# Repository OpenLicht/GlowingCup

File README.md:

# Glowing Cup

## Summary
The board measures the temperature and adjusts the color accordingly.
The Temperature is determined by three sensors, which provides the mean value
to the microcontroller. It processes and visualizes the data as a color via the built-in RGB LEDs. The board is charged wirelessly using Qi(pronounced CHEE) technology.

## Pictures
|                                    |                                |
| ---------------------              | ---------------------          |
|     |  |
|  |  |

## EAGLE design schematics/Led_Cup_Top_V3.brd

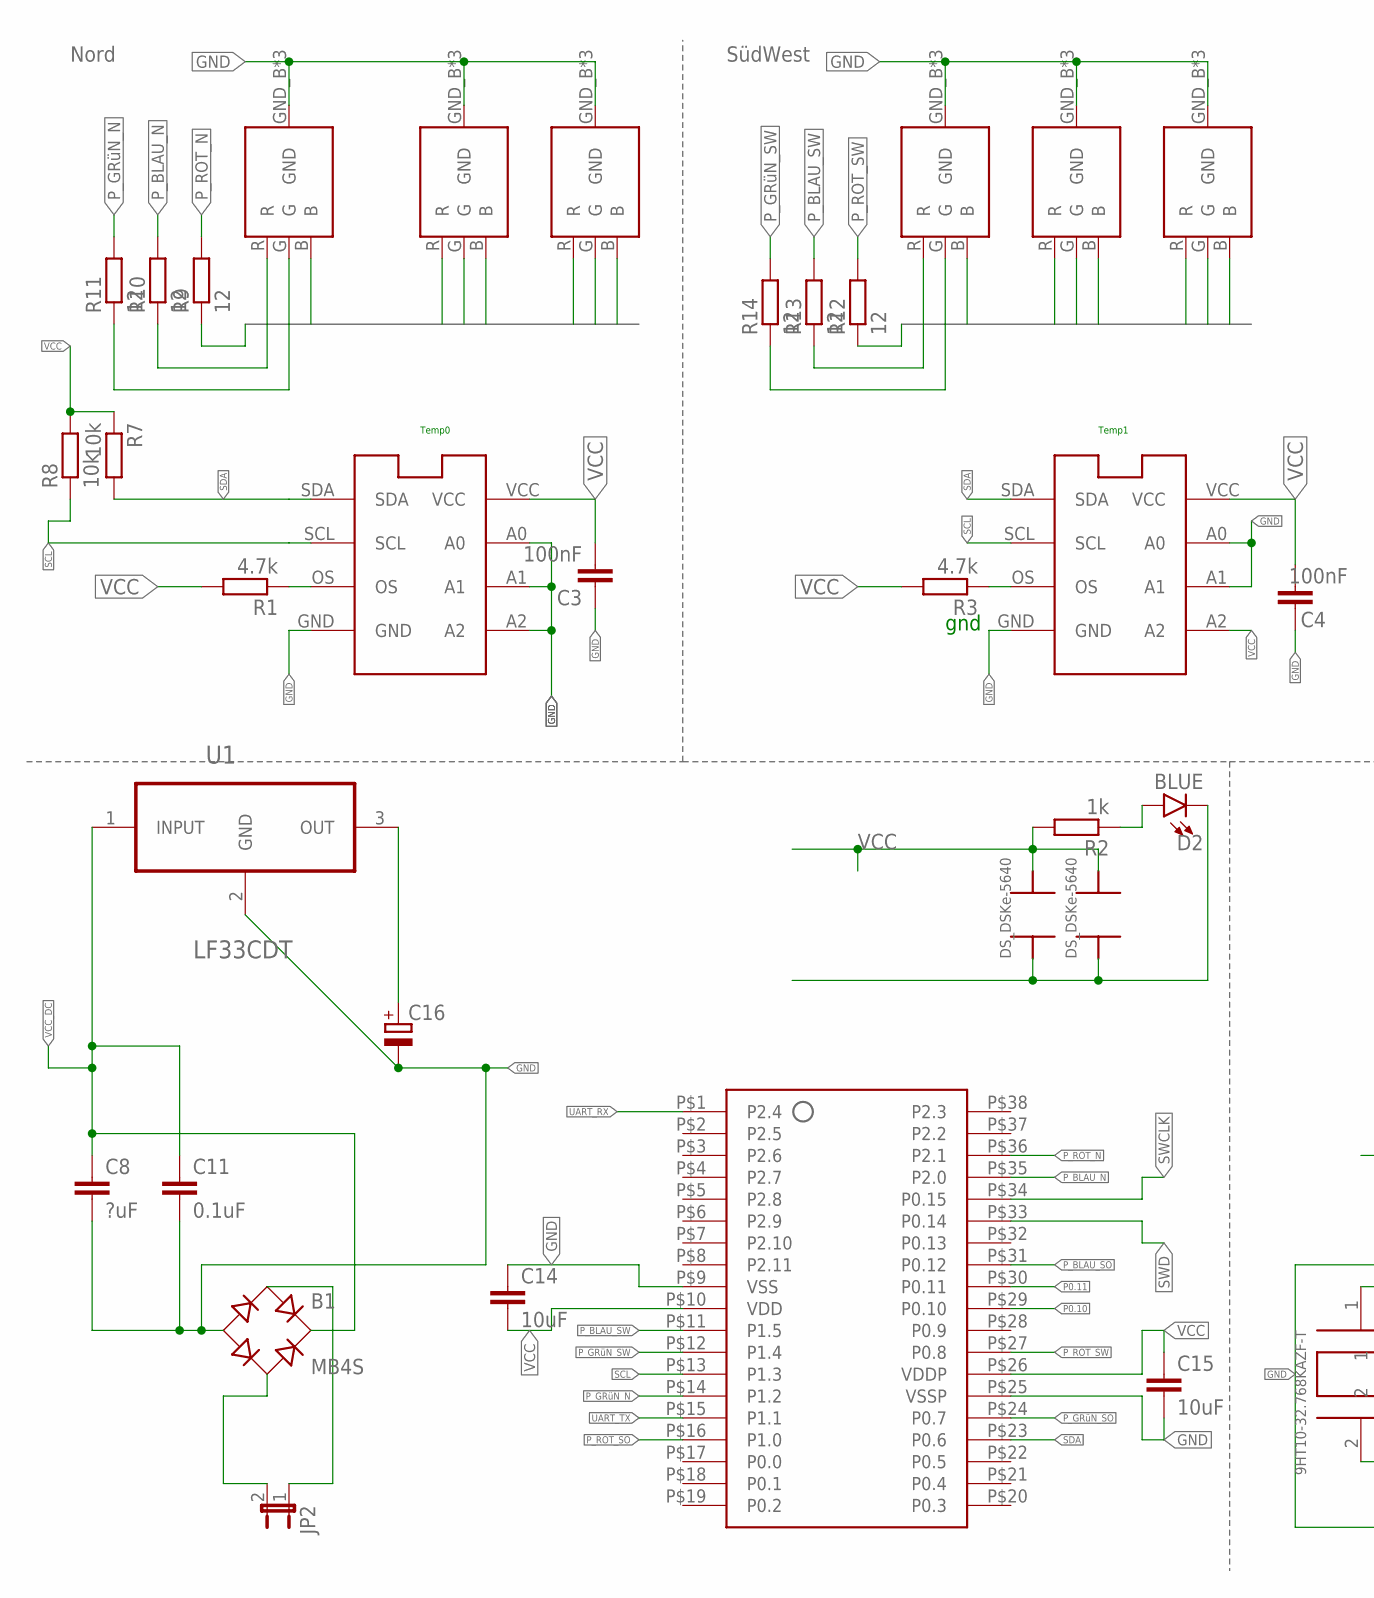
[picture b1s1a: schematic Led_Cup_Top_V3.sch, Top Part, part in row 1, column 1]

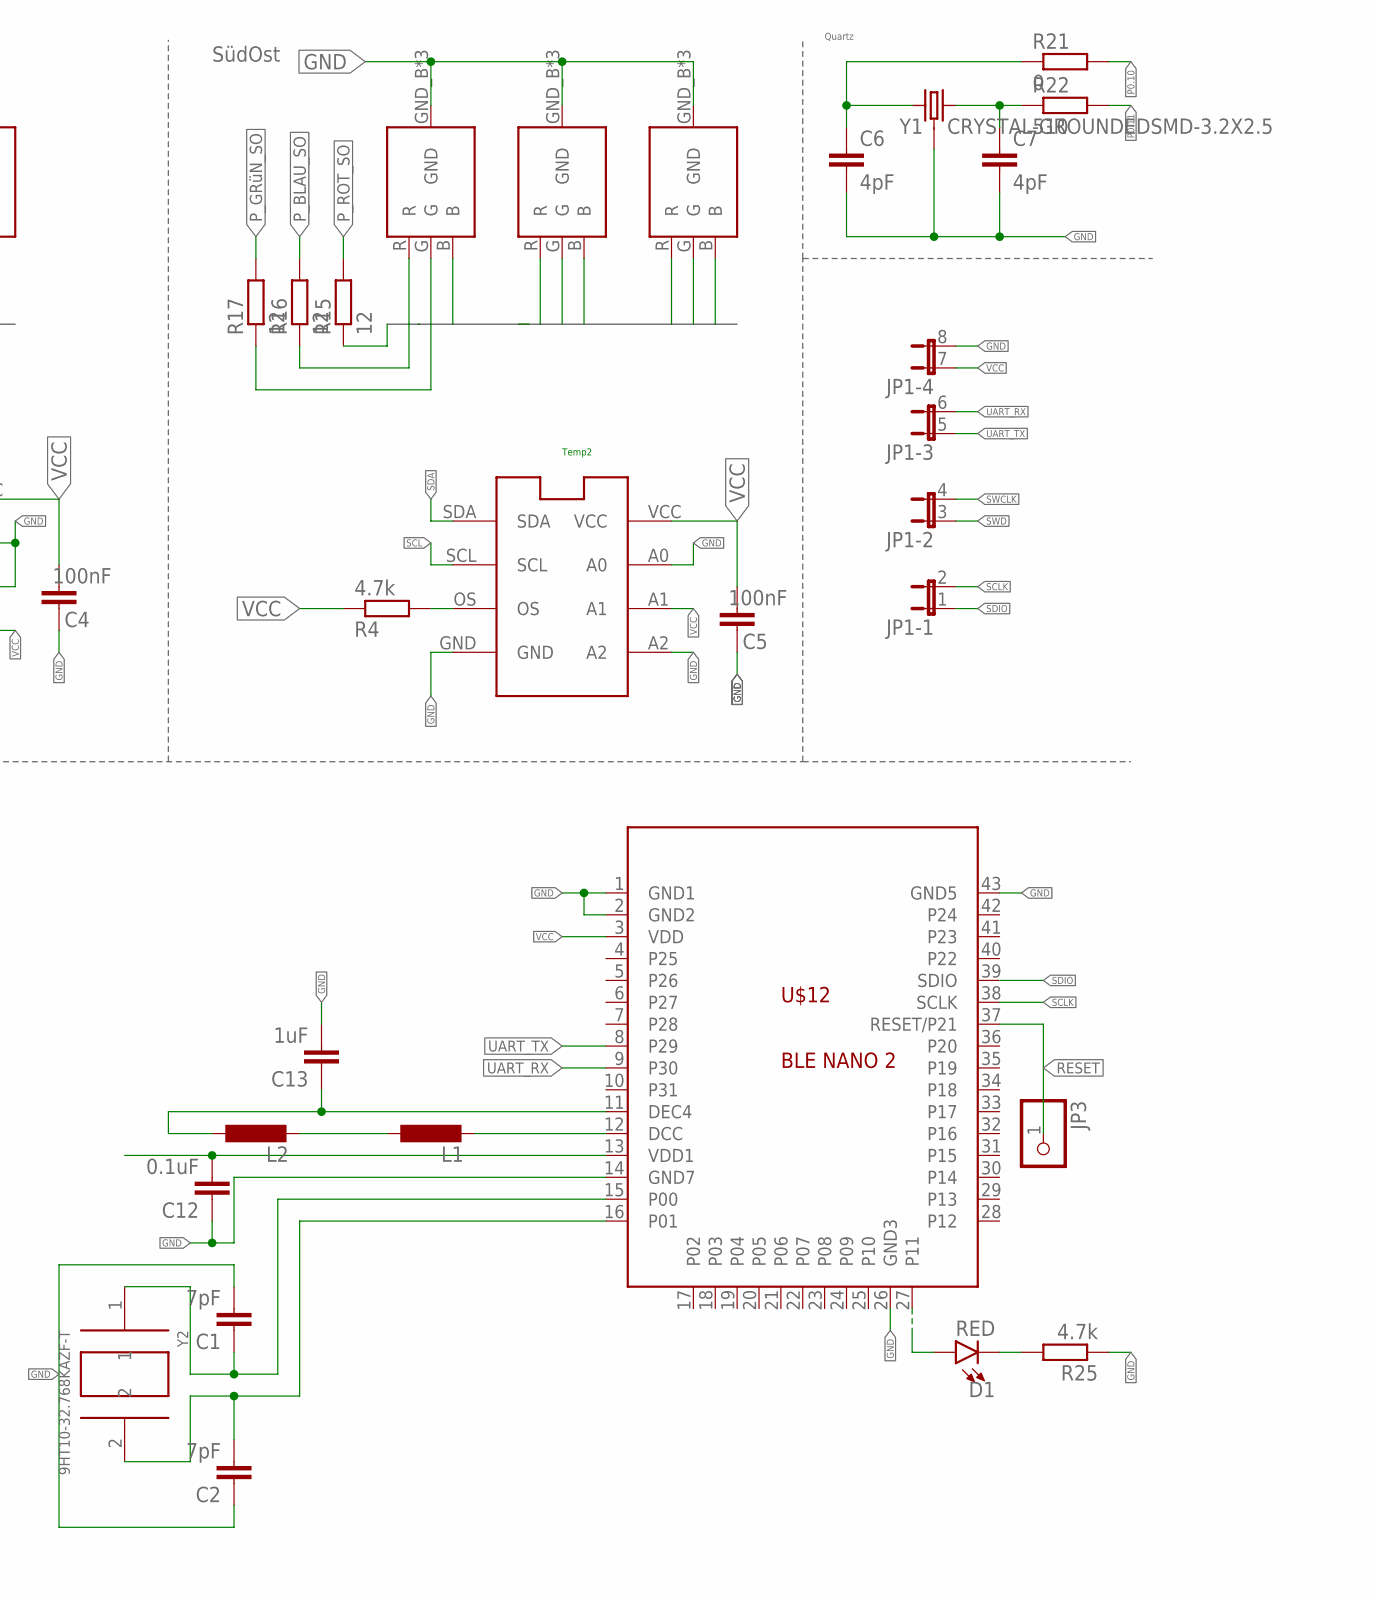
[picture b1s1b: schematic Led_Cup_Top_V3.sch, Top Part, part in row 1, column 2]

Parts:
B1: MB4S; SOIC-4
C1, C2: 7pF; C0805
C3, C4, C5: 100nF; C0805
C6, C7: 4pF; C0805
C8: ?uF; C0805
C11, C12: 0.1uF; C0805
C13: 1uF; C0603
C14, C15: 10uF; C0805
C16: CPOL-EUA/3216-18W; A/3216-18W
D1: RED; LED-0603
D2: BLUE; LED-0603
IC1: LM75Mini_TempS N; LM75MINI
IC2: LM75Mini_TempSW; LM75MINI
IC3: LM75Mini_TempSE; LM75MINI
JP1: JP4QE; JP4Q
JP2: JP1E; JP1
JP3: PINHD-1X1; 1X01
L1, L2: L-EUL2012C; L2012C
R1, R3, R4, R25: 4.7k; R0805
R2: 1k; R0805
R7, R8: 10k; R0805
R9, R10, R11, R12, R13, R14, R15, R16, R17: 12; R0805
R21: 0; R0805
R22: 510; R0805
U1: LF33CDT; TO228P972X240-3N
U$1, U$2, U$3, U$4, U$5, U$6, U$7, U$8, U$9: CREEPLCC6
U$10: XMC1400_38P
U$11, U$13: GOLDCAP
U$12: BLE NANO 2; RBT07
Y1: CRYSTAL-GROUNDEDSMD-3.2X2.5; CRYSTAL-SMD-3.2X2.5MM
Y2: 9HT10-32.768KAZF-T; XTAL320X150X75

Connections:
BLAU_N: R10.1, U$1.B, U$2.B, U$3.B
BLAU_SO: R16.1, U$7.B, U$8.B, U$9.B
BLAU_SW: R13.1, U$4.B, U$5.B, U$6.B
GND: B1.-, C1.2, C2.1, C3.1, C4.1, C5.1, C6.2, C7.2, C8.2, C11.2, C12.1, C13.2, C14.1, C15.2, C16.-, D2.C, IC1.A0, IC1.A1, IC1.A2, IC1.GND, IC2.A0, IC2.A1, IC2.GND, IC3.A0, IC3.A2, IC3.GND, JP1.8 (2), R25.1, U1.2 (GND), U$1.GND_B (GND), U$1.GND_G (GND), U$1.GND_R (GND), U$2.GND_B (GND), U$2.GND_G (GND), U$2.GND_R (GND), U$3.GND_B (GND), U$3.GND_G (GND), U$3.GND_R (GND), U$4.GND_B (GND), U$4.GND_G (GND), U$4.GND_R (GND), U$5.GND_B (GND), U$5.GND_G (GND), U$5.GND_R (GND), U$6.GND_B (GND), U$6.GND_G (GND), U$6.GND_R (GND), U$7.GND_B (GND), U$7.GND_G (GND), U$7.GND_R (GND), U$8.GND_B (GND), U$8.GND_G (GND), U$8.GND_R (GND), U$9.GND_B (GND), U$9.GND_G (GND), U$9.GND_R (GND), U$10.P$9 (VSS), U$10.P$25 (VSSP), U$11.P$1, U$12.1 (GND1), U$12.2 (GND2), U$12.14 (GND7), U$12.26 (GND3), U$12.43 (GND5), U$13.P$1, Y1.2 (3), Y1.4 (3); also elsewhere on the board
GRüN_N: R11.1, U$1.G, U$2.G, U$3.G
GRüN_SO: R17.1, U$7.G, U$8.G, U$9.G
GRüN_SW: R14.1, U$4.G, U$5.G, U$6.G
unnamed: IC1.OS, R1.1
unnamed: IC3.OS, R4.2
unnamed: IC2.OS, R3.1
unnamed 12: C16.+, U1.3 (OUT); also elsewhere on the board
unnamed: B1.~2 (AC2), JP2.2
unnamed: C7.1, R22.1, Y1.3 (2)
unnamed: C6.1, R21.1, Y1.1
unnamed: D2.A, R2.1
unnamed: B1.~1 (AC1), JP2.1
unnamed: L1.2, U$12.12 (DCC)
unnamed: L1.1, L2.2
unnamed: C13.1, L2.1, U$12.11 (DEC4)
unnamed: C1.1, U$12.15 (P00), Y2.1
unnamed: C2.2, U$12.16 (P01), Y2.2
unnamed: D1.C, R25.2
unnamed: D1.A, U$12.27 (P11)
P0.10: R21.2, U$10.P$29 (P0.10)
P0.11: R22.2, U$10.P$30 (P0.11)
P_BLAU_N: R10.2, U$10.P$35 (P2.0)
P_BLAU_SO: R16.2, U$10.P$31 (P0.12)
P_BLAU_SW: R13.2, U$10.P$11 (P1.5)
P_GRüN_N: R11.2, U$10.P$14 (P1.2)
P_GRüN_SO: R17.2, U$10.P$24 (P0.7)
P_GRüN_SW: R14.2, U$10.P$12 (P1.4)
P_ROT_N: R9.2, U$10.P$36 (P2.1)
P_ROT_SO: R15.2, U$10.P$16 (P1.0)
P_ROT_SW: R12.2, U$10.P$27 (P0.8)
RESET: JP3.1, U$12.37 (RESET/P21)
ROT_N: R9.1, U$1.R, U$2.R, U$3.R
ROT_SO: R15.1, U$7.R, U$8.R, U$9.R
ROT_SW: R12.1, U$4.R, U$5.R, U$6.R
SCL: IC1.SCL, IC2.SCL, IC3.SCL, R8.1, U$10.P$13 (P1.3)
SCLK: JP1.2, U$12.38 (SCLK)
SDA: IC1.SDA, IC2.SDA, IC3.SDA, R7.2, U$10.P$23 (P0.6)
SDIO: JP1.1, U$12.39 (SDIO)
SWCLK: JP1.4 (2), U$10.P$34 (P0.15)
SWD: JP1.3 (1), U$10.P$33 (P0.14)
UART_RX: JP1.6 (2), U$10.P$1 (P2.4), U$12.9 (P30)
UART_TX: JP1.5 (1), U$10.P$15 (P1.1), U$12.8 (P29)
VCC: C3.2, C4.2, C5.2, C12.2, C14.2, C15.1, IC1.VCC, IC2.A2, IC2.VCC, IC3.A1, IC3.VCC, JP1.7 (1), R1.2, R2.2, R3.2, R4.1, R7.1, R8.2, U$10.P$10 (VDD), U$10.P$26 (VDDP), U$11.P$2, U$12.3 (VDD), U$12.13 (VDD1), U$13.P$2; also elsewhere on the board
VCC_DC: B1.+, C8.1, C11.1, U1.1 (INPUT)

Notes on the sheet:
gnd
Nord
SüdWest
SüdOst
Quartz
Temp0
Temp1
Temp2

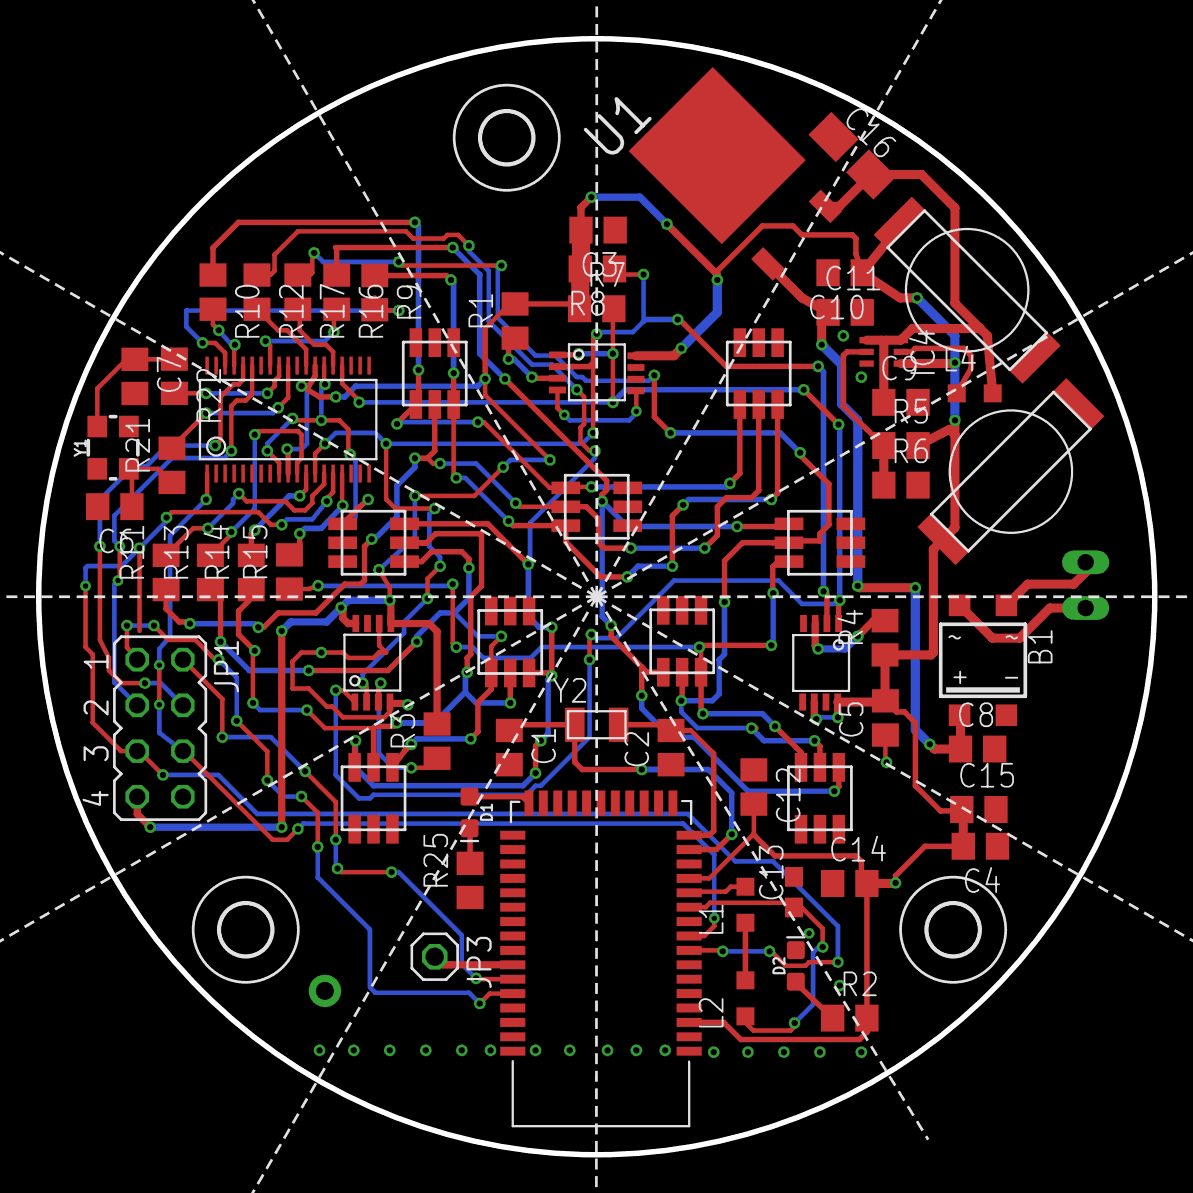
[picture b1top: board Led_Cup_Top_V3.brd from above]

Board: 2 copper layers, 62.0 x 62.0 mm, 68 parts (1 on the bottom side), 50 nets.

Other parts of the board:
C9, C10: ?uF; C0805
IC4: TPS61220DCKT; SOIC65P210X95-6N
L4: L2012C
R5: 1M; R0805
R6: 178k; R0805
U$15, U$16, U$17: 2,8

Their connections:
GND: C9.2, C10.2, IC4.3, R6.2; also elsewhere on the board
unnamed 12: C9.1, IC4.1, IC4.6, L4.2; also elsewhere on the board
unnamed: IC4.5, L4.1
unnamed: IC4.2, R5.1, R6.1
VCC: C10.1, IC4.4, R5.2; also elsewhere on the board

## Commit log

2019-12-03 pictures

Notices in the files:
parts and their libraries:
SparkFun-Clocks: Licensing: Creative Commons ShareAlike 4.0 International - https://creativecommons.org/licenses/by-sa/4.0
